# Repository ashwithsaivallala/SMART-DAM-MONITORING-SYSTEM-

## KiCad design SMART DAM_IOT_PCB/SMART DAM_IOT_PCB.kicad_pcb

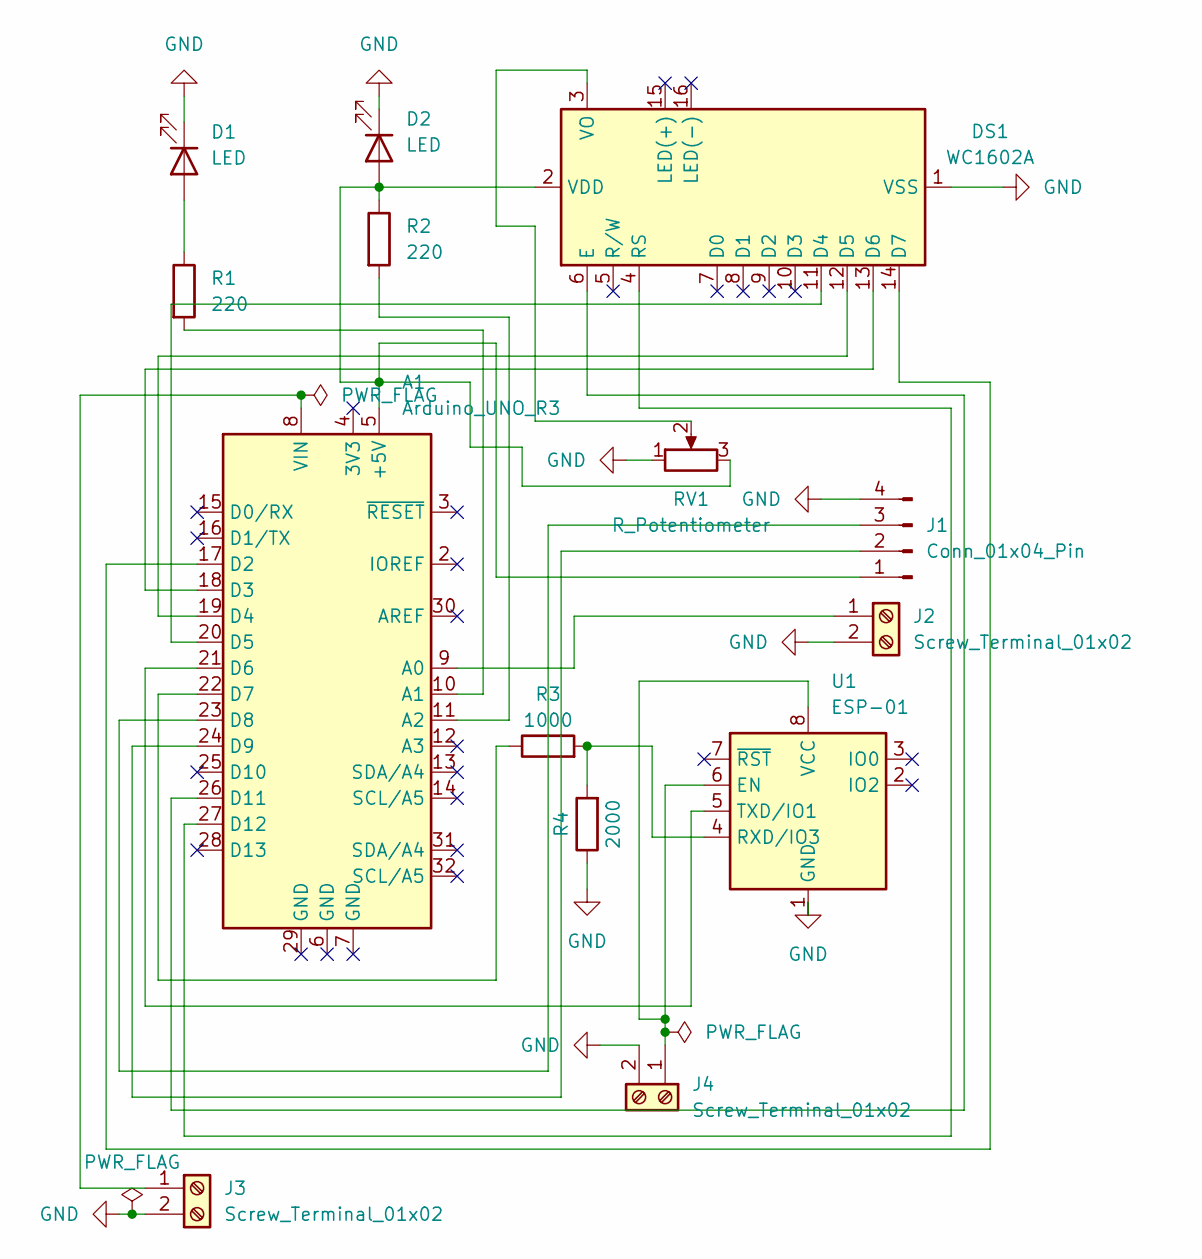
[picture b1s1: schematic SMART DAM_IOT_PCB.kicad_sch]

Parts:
A1: Arduino_UNO_R3
D1, D2: LED; LED_D5.0mm
DS1: WC1602A; PinHeader_1x16_P2.54mm_Vertical
J1: Conn_01x04_Pin; PinHeader_1x04_P2.54mm_Vertical
J2, J3, J4: Screw_Terminal_01x02; TerminalBlock_Phoenix_PT-1,5-2-5.0-H_1x02_P5.00mm_Horizontal
R1, R2: 220; R_Axial_DIN0207_L6.3mm_D2.5mm_P7.62mm_Horizontal
R3: 1000; R_Axial_DIN0207_L6.3mm_D2.5mm_P7.62mm_Horizontal
R4: 2000; R_Axial_DIN0207_L6.3mm_D2.5mm_P7.62mm_Horizontal
RV1: R_Potentiometer; Potentiometer_Bourns_3386F_Vertical
U1: ESP-01; PinHeader_2x04_P2.54mm_Horizontal

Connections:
GND: D1.1 (K), D2.1 (K), DS1.1 (VSS), J1.4, J2.2, J3.2, J4.2, R4.1, RV1.1, U1.1 (GND)
unnamed: A1.5 (+5V), D2.2 (A), DS1.2 (VDD), J1.1, R2.1, RV1.3
unnamed: A1.9 (A0), J2.1
unnamed: A1.10 (A1), R1.2
unnamed: A1.11 (A2), R2.2
unnamed: A1.17 (D2), DS1.14 (D7)
unnamed: A1.18 (D3), DS1.13 (D6)
unnamed: A1.19 (D4), DS1.12 (D5)
unnamed: A1.20 (D5), DS1.11 (D4)
unnamed: A1.21 (D6), U1.5 (TXD/IO1)
unnamed: A1.22 (D7), R3.1
unnamed: A1.23 (D8), J1.3
unnamed: A1.24 (D9), J1.2
unnamed: A1.26 (D11), DS1.6 (E)
unnamed: A1.27 (D12), DS1.4 (RS)
unnamed: A1.8 (VIN), J3.1
unnamed: D1.2 (A), R1.1
unnamed: DS1.3 (VO), RV1.2
unnamed: J4.1, U1.6 (EN), U1.8 (VCC)
unnamed: R3.2, R4.2, U1.4 (RXD/IO3)

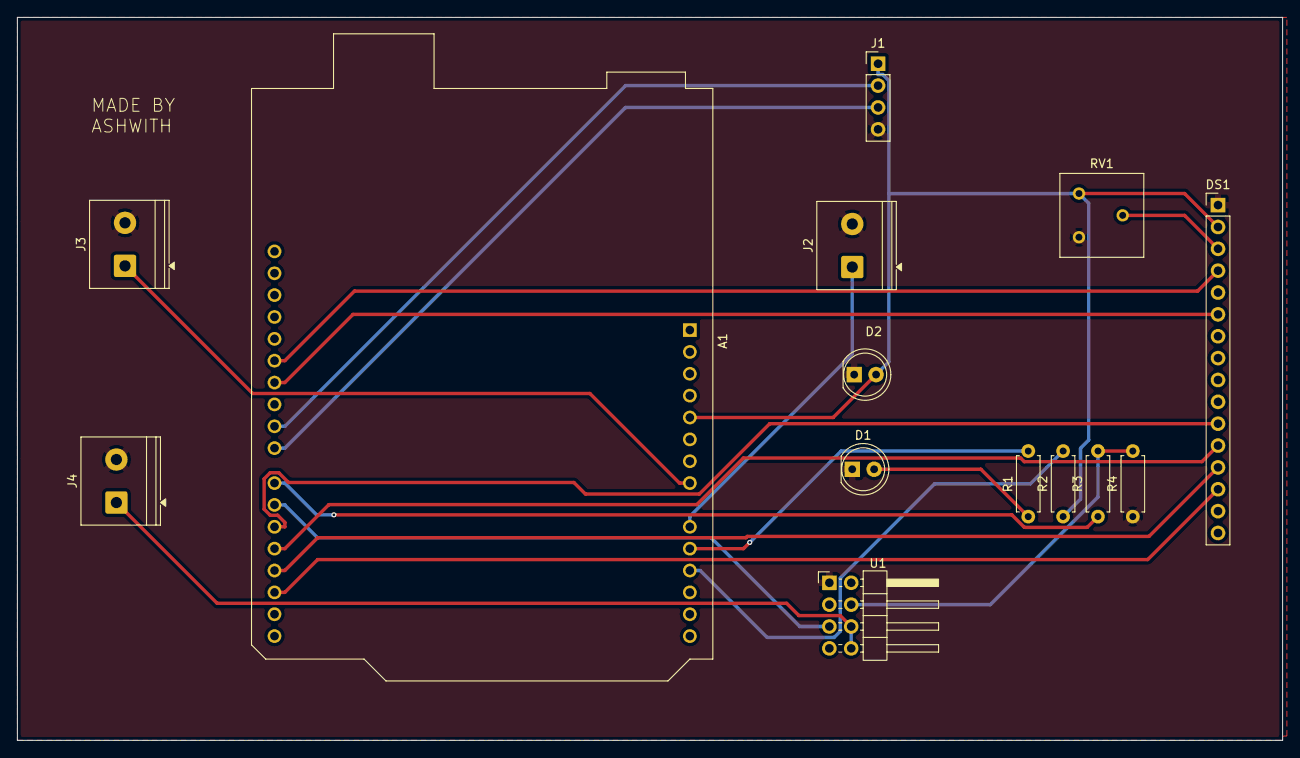
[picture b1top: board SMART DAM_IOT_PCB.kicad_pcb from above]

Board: 2 copper layers, 147.0 x 84.0 mm, 14 parts (0 on the bottom side), 20 nets.

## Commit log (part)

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2026-06-28 SMART DAM MONITORING SYSTEM CODE
